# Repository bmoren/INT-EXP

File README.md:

# INT EXP

screen &amp; physical interaction experimentation board

based on [v-usb](https://www.obdev.at/products/vusb/index.html) and the [ATtiny85](http://www.atmel.com/devices/attiny85.aspx)

with thanks to the [easy logger project](https://www.obdev.at/products/vusb/easylogger.html) and the [4 key keyboard project](http://blog.flipwork.nl/?x=entry:entry100224-003937)

[Build of Materials](https://docs.google.com/spreadsheets/d/1fC4rKzH0t7pgVtuNgmvmoYLOOsRQa8CITz7sNQLkrys/edit#gid=0)

### to compile and upload:
1. install [crosspack](https://www.obdev.at/products/crosspack/index.html)
1. pop an [ATtiny85](http://www.atmel.com/devices/attiny85.aspx) into the [usbtiny](https://www.sparkfun.com/products/11801) programmer
1. `cd` to this directory
1. `make fuse` Make the temporary 3 pin fuses with i/o on pin 4 for testing, (For the final fuse config, see below.)
1. `make flash` Flash the main.c file to the board.
1. `make resetfuse`
  + uses the final 4 pin i/o for final deployment. NOTE: this will disable the ATtiny from being re-programmable without a high voltage programmer. This must be completed after `make flash` or you will not be able to program the board!
1. `make clean` Delete all of the files used to build the main.hex file for programming.

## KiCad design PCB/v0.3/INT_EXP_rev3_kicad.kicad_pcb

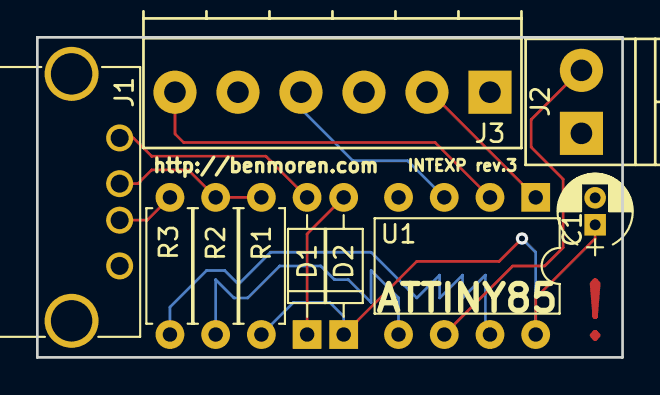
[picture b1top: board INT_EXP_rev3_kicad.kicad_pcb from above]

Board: 2 copper layers, 32.5 x 17.8 mm, 10 parts (0 on the bottom side), 12 nets.

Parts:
C1: 0.1uf; CP_Radial_D4.0mm_P1.50mm
D1, D2: 1N4148; D_DO-35_SOD27_P7.62mm_Horizontal
J1: USB_A
J2: TOGGLE; TerminalBlock_Phoenix_PT-3.5mm_2pol
J3: ABC123; TerminalBlock_Phoenix_PT-3.5mm_6pol
R1: 1.5k; R_Axial_DIN0207_L6.3mm_D2.5mm_P7.62mm_Horizontal
R2, R3: 68; R_Axial_DIN0207_L6.3mm_D2.5mm_P7.62mm_Horizontal
U1: ATTINY85-20PU; DIP-8_W7.62mm

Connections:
GNDREF: C1.2, J1.4, J2.1, J3.1, J3.3, J3.5, U1.4
unnamed: C1.1, D2.1, R1.1, U1.8
unnamed: D1.1, D2.2
unnamed: D1.2, J1.1
unnamed: J1.2, R1.2, R2.2
unnamed: J1.3, R3.2
unnamed: J2.2, U1.6
unnamed: J3.2, U1.1
unnamed: J3.4, U1.3
unnamed: J3.6, U1.2
unnamed: R2.1, U1.5
unnamed: R3.1, U1.7

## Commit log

2016-06-10 init
2016-06-27 abc/123 switch working
2016-06-27 add final fuse to makefile
2016-07-24 added v0.1 of the PCB
2016-08-07 added board image and changed name of repo
2016-08-09 resolving conflict
2016-08-09 adding image
2016-08-26 v0.2 pcb
2016-09-22 fixed key order
2016-12-01 fix readme image
2016-12-08 adding examples
2016-12-08 init gh-pages
2017-11-29 rev3
